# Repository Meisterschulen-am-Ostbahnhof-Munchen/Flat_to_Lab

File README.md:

# Flat_to_Lab
Board to adopt 4mm Laboratory Socket to 6.3mm Flat Socket

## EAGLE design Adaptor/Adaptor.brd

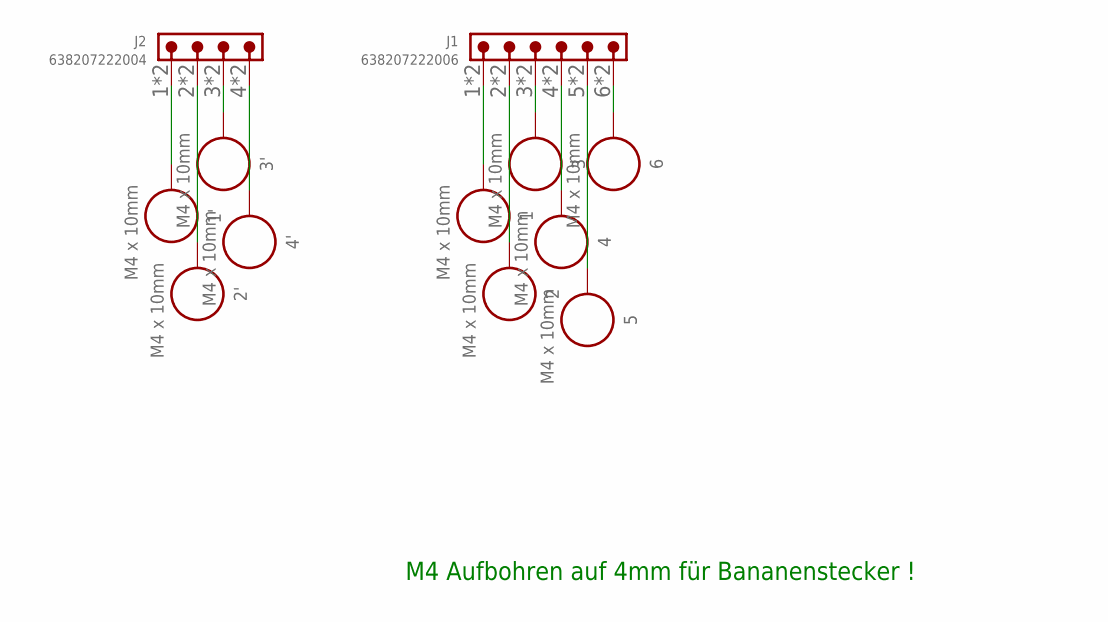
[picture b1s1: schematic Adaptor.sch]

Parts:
1, 1', 2, 2', 3, 3', 4, 4', 5, 6: M4 x 10mm; WA-SMSI_9774100482
J1: 638207222006
J2: 638207222004

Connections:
unnamed: 1.1, J1.1, J1.A1 (1)
unnamed: 2.1, J1.2, J1.A2 (2)
unnamed: 3.1, J1.3, J1.A3 (3)
unnamed: 4.1, J1.4, J1.A4 (4)
unnamed: 5.1, J1.5, J1.A5 (5)
unnamed: 6.1, J1.6, J1.A6 (6)
unnamed: 1'.1, J2.1, J2.A1 (1)
unnamed: 2'.1, J2.2, J2.A2 (2)
unnamed: 4'.1, J2.4, J2.A4 (4)
unnamed: 3'.1, J2.3, J2.A3 (3)

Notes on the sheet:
M4 Aufbohren auf 4mm für Bananenstecker !

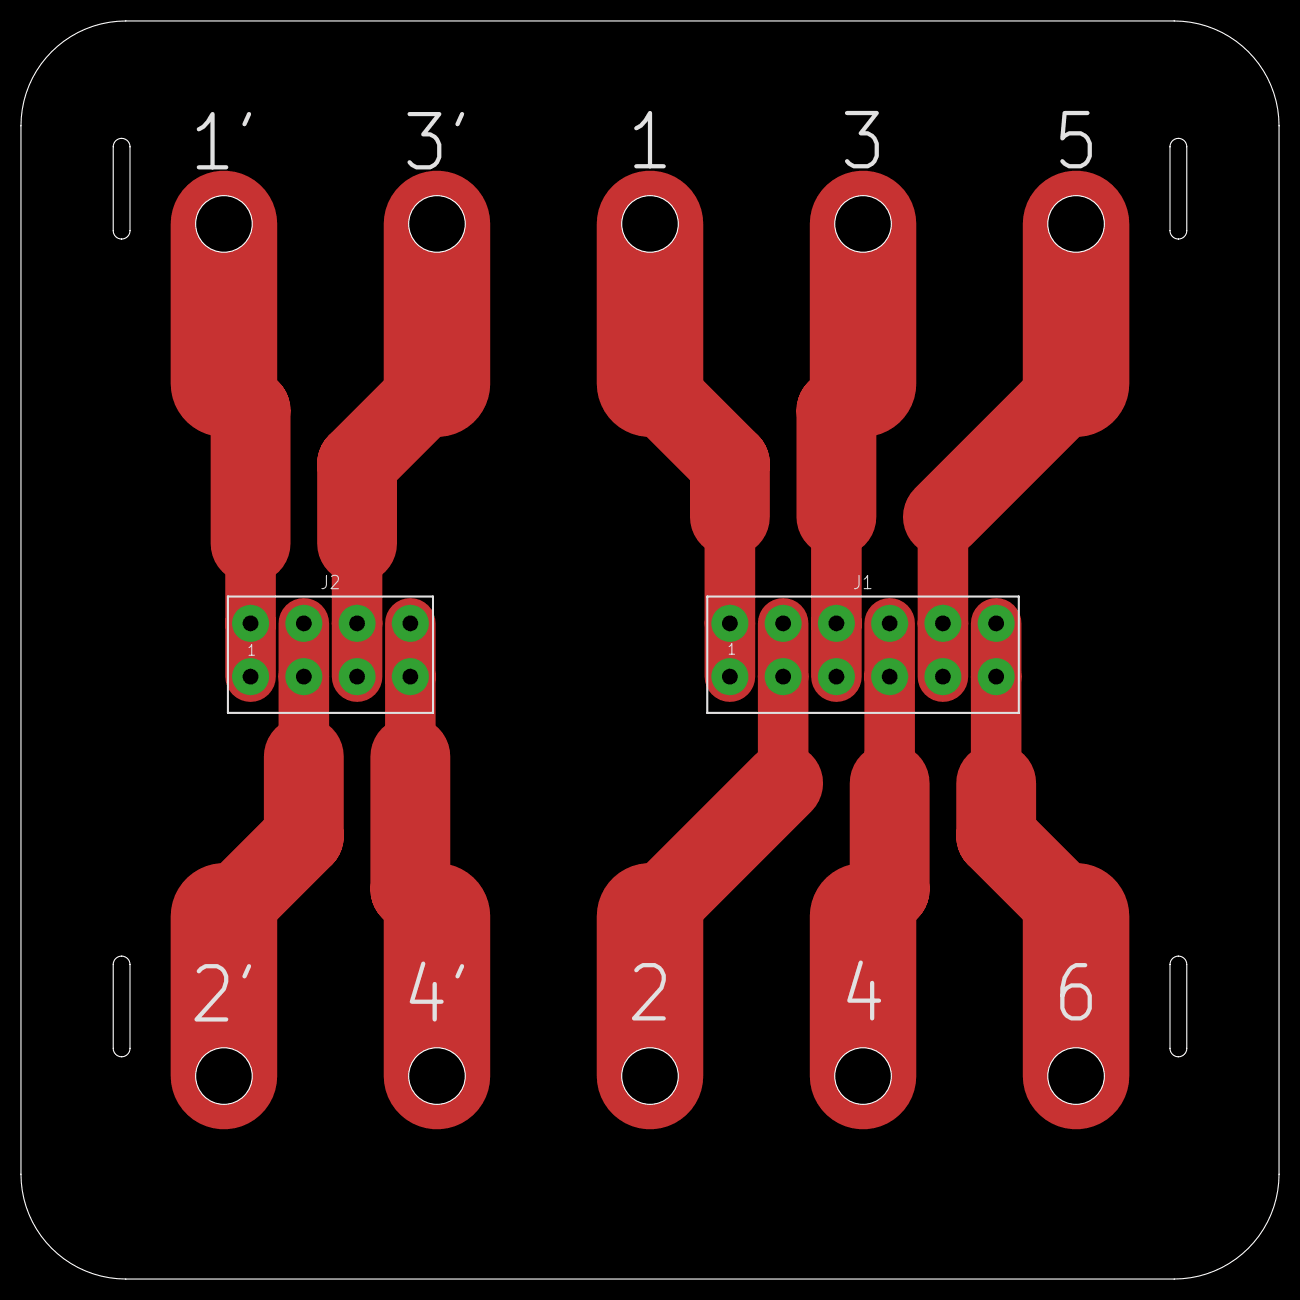
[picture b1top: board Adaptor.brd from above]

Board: 2 copper layers, 120.0 x 120.0 mm, 12 parts (0 on the bottom side), 10 nets.

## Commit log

2021-10-22 gitflow-feature-stash: First
2021-10-22 cleanm up.
2021-10-22 finish !
2021-11-09 gerber

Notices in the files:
parts and their libraries:
Wurth_Assembly_WA-SMSI: Copyright: Würth Elektronik
